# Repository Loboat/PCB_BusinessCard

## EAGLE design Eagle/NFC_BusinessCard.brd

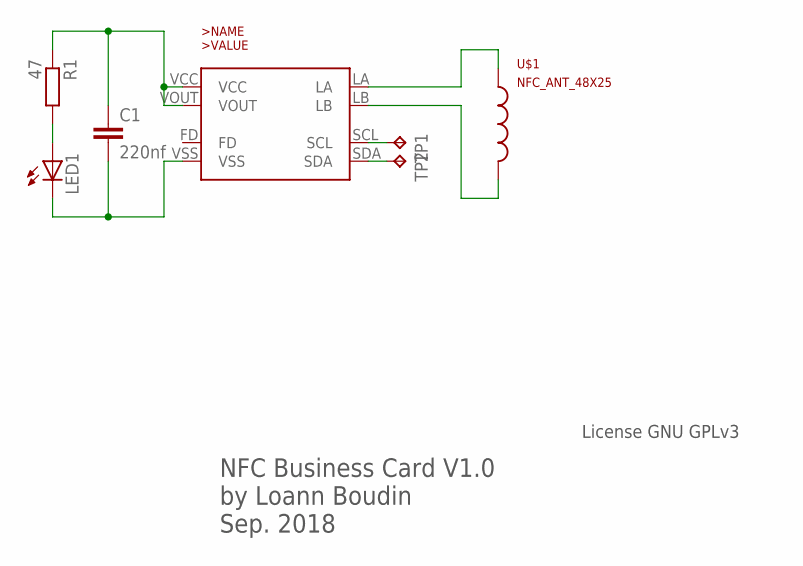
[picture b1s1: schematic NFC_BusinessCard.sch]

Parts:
C1: 220nf; C0603
LED1: LEDSML0805; SML0805
NT3H1101: NT3H1101; XQFN8
R1: 47; R0603
TP1, TP2: TPTP06R; TP06R
U$1: NFC_ANT_48X25

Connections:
unnamed: NT3H1101.LA, U$1.A
unnamed: NT3H1101.LB, U$1.B, U$1.P$3 (B)
unnamed: C1.1, NT3H1101.VCC, NT3H1101.VOUT, R1.1
unnamed: LED1.A, R1.2
unnamed: NT3H1101.SDA, TP2.TP
unnamed: C1.2, LED1.C, NT3H1101.VSS
unnamed: NT3H1101.SCL, TP1.TP

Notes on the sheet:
NFC Business Card V1.0 by Loann Boudin Sep. 2018
License GNU GPLv3

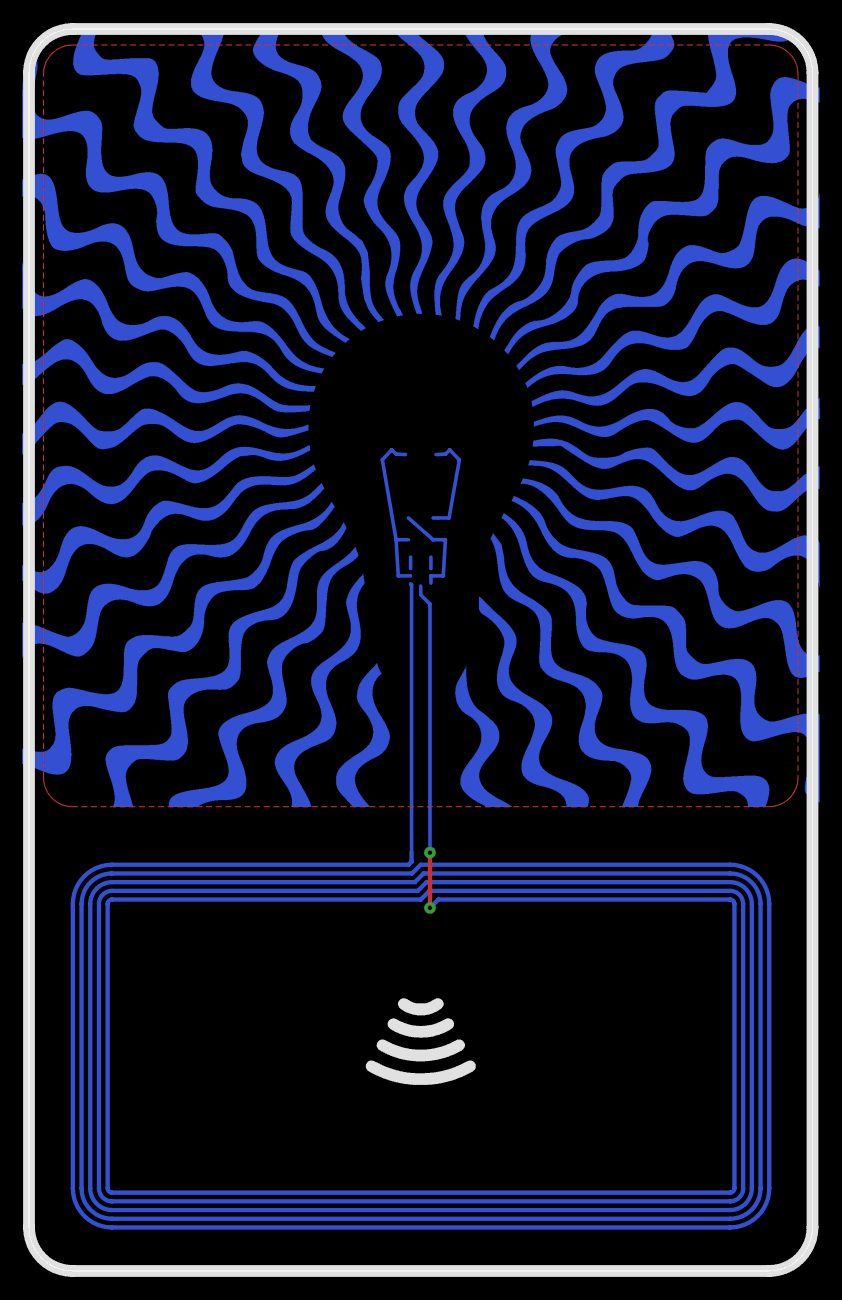
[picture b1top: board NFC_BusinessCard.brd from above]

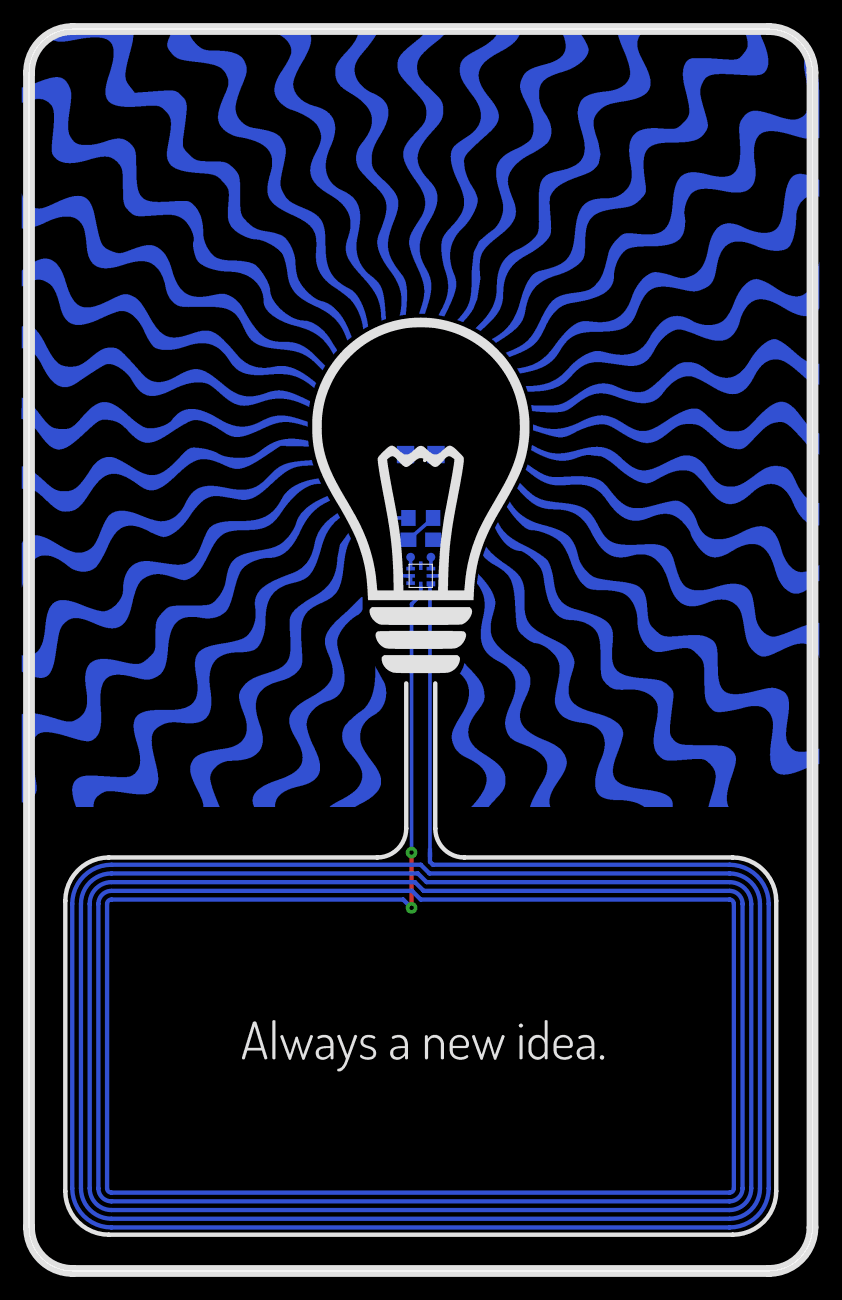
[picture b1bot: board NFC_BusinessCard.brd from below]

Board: 2 copper layers, 54.0 x 85.6 mm, 7 parts (6 on the bottom side), 7 nets.

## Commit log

2018-10-02 Add files via upload
    First commit
